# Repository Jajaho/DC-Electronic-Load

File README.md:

# DC-Electronic-Load
Digitally controlled dc electronic load.  

To cut costs, the core idea is to use multiple smaller low-cost MOSFETs in parallel instead of a single higher-power device.
Since the current through a semiconductor has a positive temperature coefficient this presents a novel engineering challenge. An unsuitable design could risk a thermal runaway event where a single transistor would handle increasingly larger currents until failure. To prevent such a catastrophic event a circuit to ensure equal current distribution is implemented.  

The instrument should feature constant current, voltage and power modes. Over-voltage and current protection is also desired.

This project was initially started in Eagle ECAD on 28.05.2019 but was never implemented.

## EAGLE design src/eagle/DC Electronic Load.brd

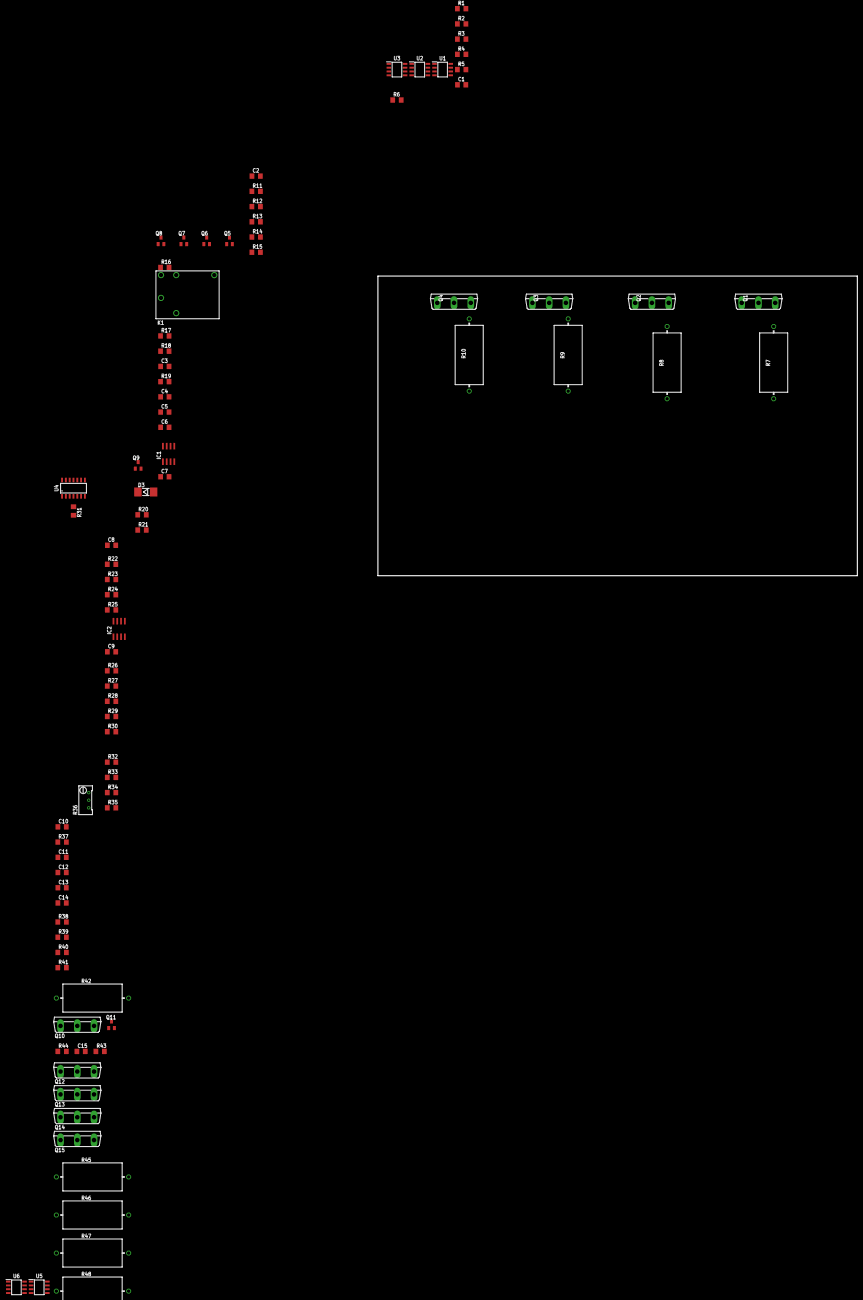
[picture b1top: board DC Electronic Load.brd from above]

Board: 2 copper layers, 160.0 x 100.0 mm, 88 parts (0 on the bottom side), 52 nets, no tracks yet.

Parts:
C1, C2, C3, C10: C1206
C4, C5, C6, C8, C9: 100n; C1206
C7: 1oon; C1206
C11, C12, C13, C14, C15: 10nF; C1206
D3: 1N4001; MELF-MLL41
IC1: LM393D; SO08
IC2: TL072D; SO08
K1: AZ8-FORM-C; AZ8
Q1, Q2, Q3, Q4, Q10, Q12, Q13, Q14, Q15: IRFP240; TO247BV
Q5, Q6, Q7, Q8, Q9, Q11: NPN; SOT23
R1, R2, R3, R4, R5, R6, R11, R16, R17, R18, R19, R20, R21, R22, R23, R24, R25, R30, R31, R37: R1206
R7, R8, R9, R10, R42, R45, R46, R47, R48: 1R; VTA53
R12, R13, R14, R15, R43: 2K2; R1206
R26, R27, R28, R29, R33: 10k; R1206
R32, R35: 3k; R1206
R34: 1M; R1206
R36: RTRIM64W
R38, R39, R40, R41, R44: 100R; R1206
U1, U2: AD8628; SOIC-8
U3, U5, U6: OPA196; SOIC-8
U4: SN74AHC08; SOIC−14

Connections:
+5V: C4.1, C5.1, C7.1, C8.1, C9.1, IC1.8, IC2.8, R30.2, R31.2, R32.2, R35.1, U1.7, U2.7, U4.14
+12V: C6.1, D3.C, K1.2, U3.7
+VLOAD: Q1.D, Q2.D, Q3.D, Q4.D, R18.2, R24.2, R37.2
-5V: R38.1, R39.1, R40.1, R41.1, R44.1
-VLOAD: C3.1, K1.3, R19.2, R22.2, U2.2, U2.6
GND: C1.2, C3.2, C4.2, C5.2, C6.2, C7.2, C8.2, C9.2, IC1.4, IC2.4, K1.1, Q9.2, R1.1, R3.2, R6.1, R17.1, R23.1, R25.1, R26.1, R36.1, R36.2, U1.4, U2.4, U3.4, U4.7
ISENSE: IC1.2, R5.2, R11.1, R28.1, U3.2
unnamed: C1.1, R2.2, R5.1, U1.6
unnamed: R1.2, R2.1, U1.2
unnamed: R3.1, R4.2, U1.3
unnamed: C10.2, R4.1, R6.2, R7.1, R8.1, R9.1, R10.1
unnamed: IC1.6, R22.1, R23.2
unnamed: IC1.5, R24.1, R25.2
unnamed: C2.1, R11.2
unnamed: C2.2, R16.1, U3.6
unnamed: Q1.S, Q5.1, R7.2
unnamed: Q2.S, Q6.1, R8.2
unnamed: Q3.S, Q7.1, R9.2
unnamed: Q4.S, Q8.1, R10.2
unnamed: C11.1, C12.1, C13.1, C14.1, R12.2, R13.2, R14.2, R15.2, R16.2
unnamed: C11.2, Q1.G, Q5.3, R12.1
unnamed: C12.2, Q2.G, Q6.3, R13.1
unnamed: C13.2, Q3.G, Q7.3, R14.1
unnamed: C14.2, Q4.G, Q8.3, R15.1
unnamed: IC1.7, R32.1, U4.2
unnamed: Q6.2, R39.2
unnamed: R17.2, R18.1, U2.3
unnamed: D3.A, K1.5, R20.2
unnamed: Q9.3, R20.1
unnamed: U4.3, U4.4
unnamed: Q9.1, R21.2
unnamed: R31.1, U4.5
unnamed: IC1.1, R34.2, R35.2, U4.1
unnamed: IC2.3, R28.2, R29.2
unnamed: IC2.2, R26.2, R27.1
unnamed: IC2.1, R27.2, R33.1
unnamed: IC1.3, R33.2, R34.1
unnamed: R29.1, R30.1, R36.3
unnamed: R21.1, U4.6
unnamed: C10.1, R37.1
unnamed: Q7.2, R40.2
unnamed: Q8.2, R41.2
unnamed: Q5.2, R38.2
unnamed: Q10.S, Q11.1, R42.2
unnamed: C15.1, R43.2
unnamed: C15.2, Q10.G, Q11.3, R43.1
unnamed: Q11.2, R44.2
unnamed: Q12.G, U5.6
unnamed: Q12.S, R45.2, U5.2
unnamed: Q13.S, R46.2, U6.2
unnamed: Q13.G, U6.6
unnamed: U5.3, U6.3

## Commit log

2023-07-06 Add eagle project files
2023-07-13 Add kicad project imported from eagle
2023-07-13 Tidy up kicad schematic
